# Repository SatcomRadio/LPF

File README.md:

# Low pass filter board

This repo consists of a board for making a low pass filter (LPF). 

You can use it with your own coils and RF capacitors for your desired frequency.

You can use a metal box like [this one](https://www.aliexpress.com/item/1005001849603652.html) of size 92x38x31mm to store it.

------------------------

In order to make it work on satcom frequencies you will need:

```
3x 11pF RF capacitors (https://aliexpress.com/item/1005006664008969.html)
0.8mm enameled copper wire

Optional: Storage box (https://www.aliexpress.com/item/1005001849603652.html)
```

Schema:

Side coils instructions:  

```
0.8mm enameled wire, 3.5mm diameter, 2 turns spreaded
```

Middle coils instructions:  

```
0.8mm enameled wire, 4mm diameter, 5 turns spreaded
```

After adjusting with the nanovna you should be able to get this graph:

------------------------

## Ordering the PCB:

Download the Gerber file from this repo and order it a jlcpcb with the default options.  
The only option I've changed is to remove the manufacture code mark

#### Please make sure to visit the [satcom radio website](https://satcomradio.github.io/) for more information

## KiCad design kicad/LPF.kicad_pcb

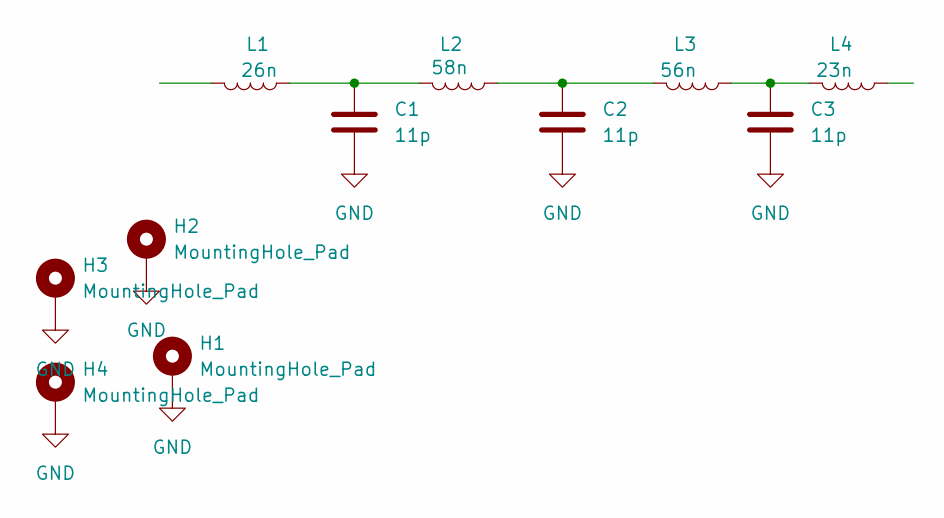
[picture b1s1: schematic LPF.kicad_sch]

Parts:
C1, C2, C3: 11p; RFCap_S
H1, H2, H3, H4: MountingHole_Pad; MountingHole_3.2mm_M3_Pad_Via
L1: 26n; Wound_Inductor_S
L2: 58n; Wound_Inductor_S
L3: 56n; Wound_Inductor_S
L4: 23n; Wound_Inductor_S

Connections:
GND: C1.2, C2.2, C3.2, H1.1, H2.1, H3.1, H4.1
unnamed: C1.1, L1.1, L2.1
unnamed: C2.1, L2.2, L3.1
unnamed: C3.1, L3.2, L4.1

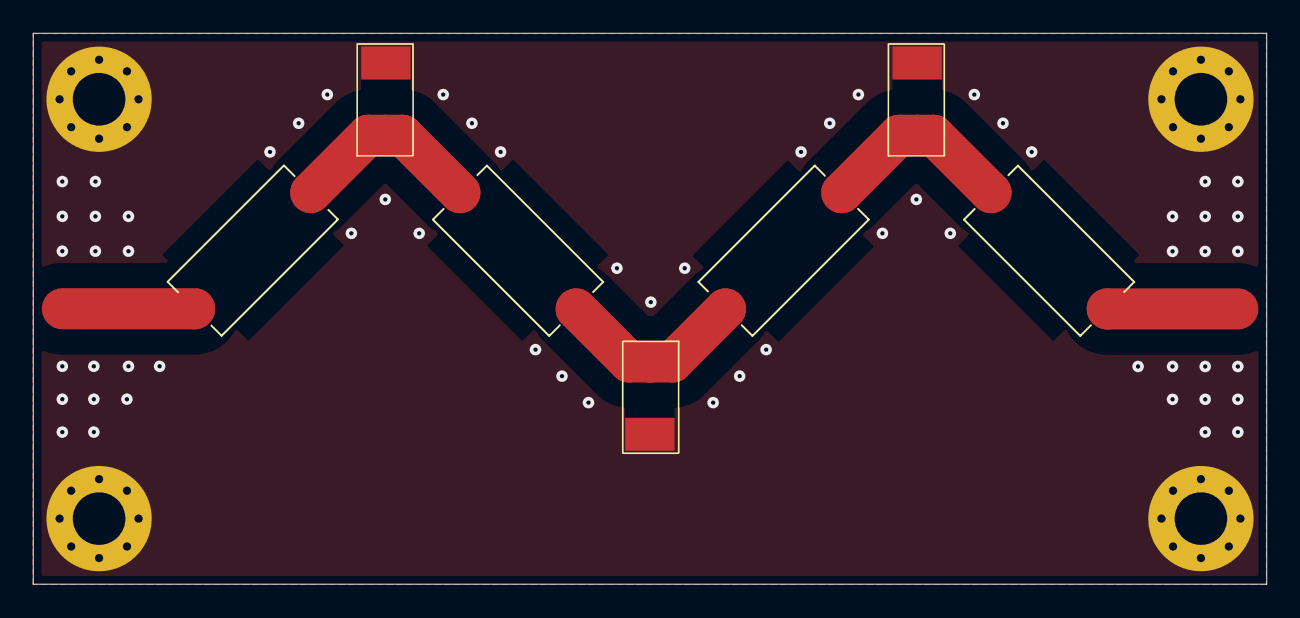
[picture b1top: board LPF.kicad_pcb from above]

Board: 2 copper layers, 75.0 x 33.5 mm, 11 parts (0 on the bottom side), 4 nets.

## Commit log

2025-06-26 File commit
2025-06-26 Added box data
2025-06-26 Added box image
2025-07-08 Use 11pF instead of 12pF
